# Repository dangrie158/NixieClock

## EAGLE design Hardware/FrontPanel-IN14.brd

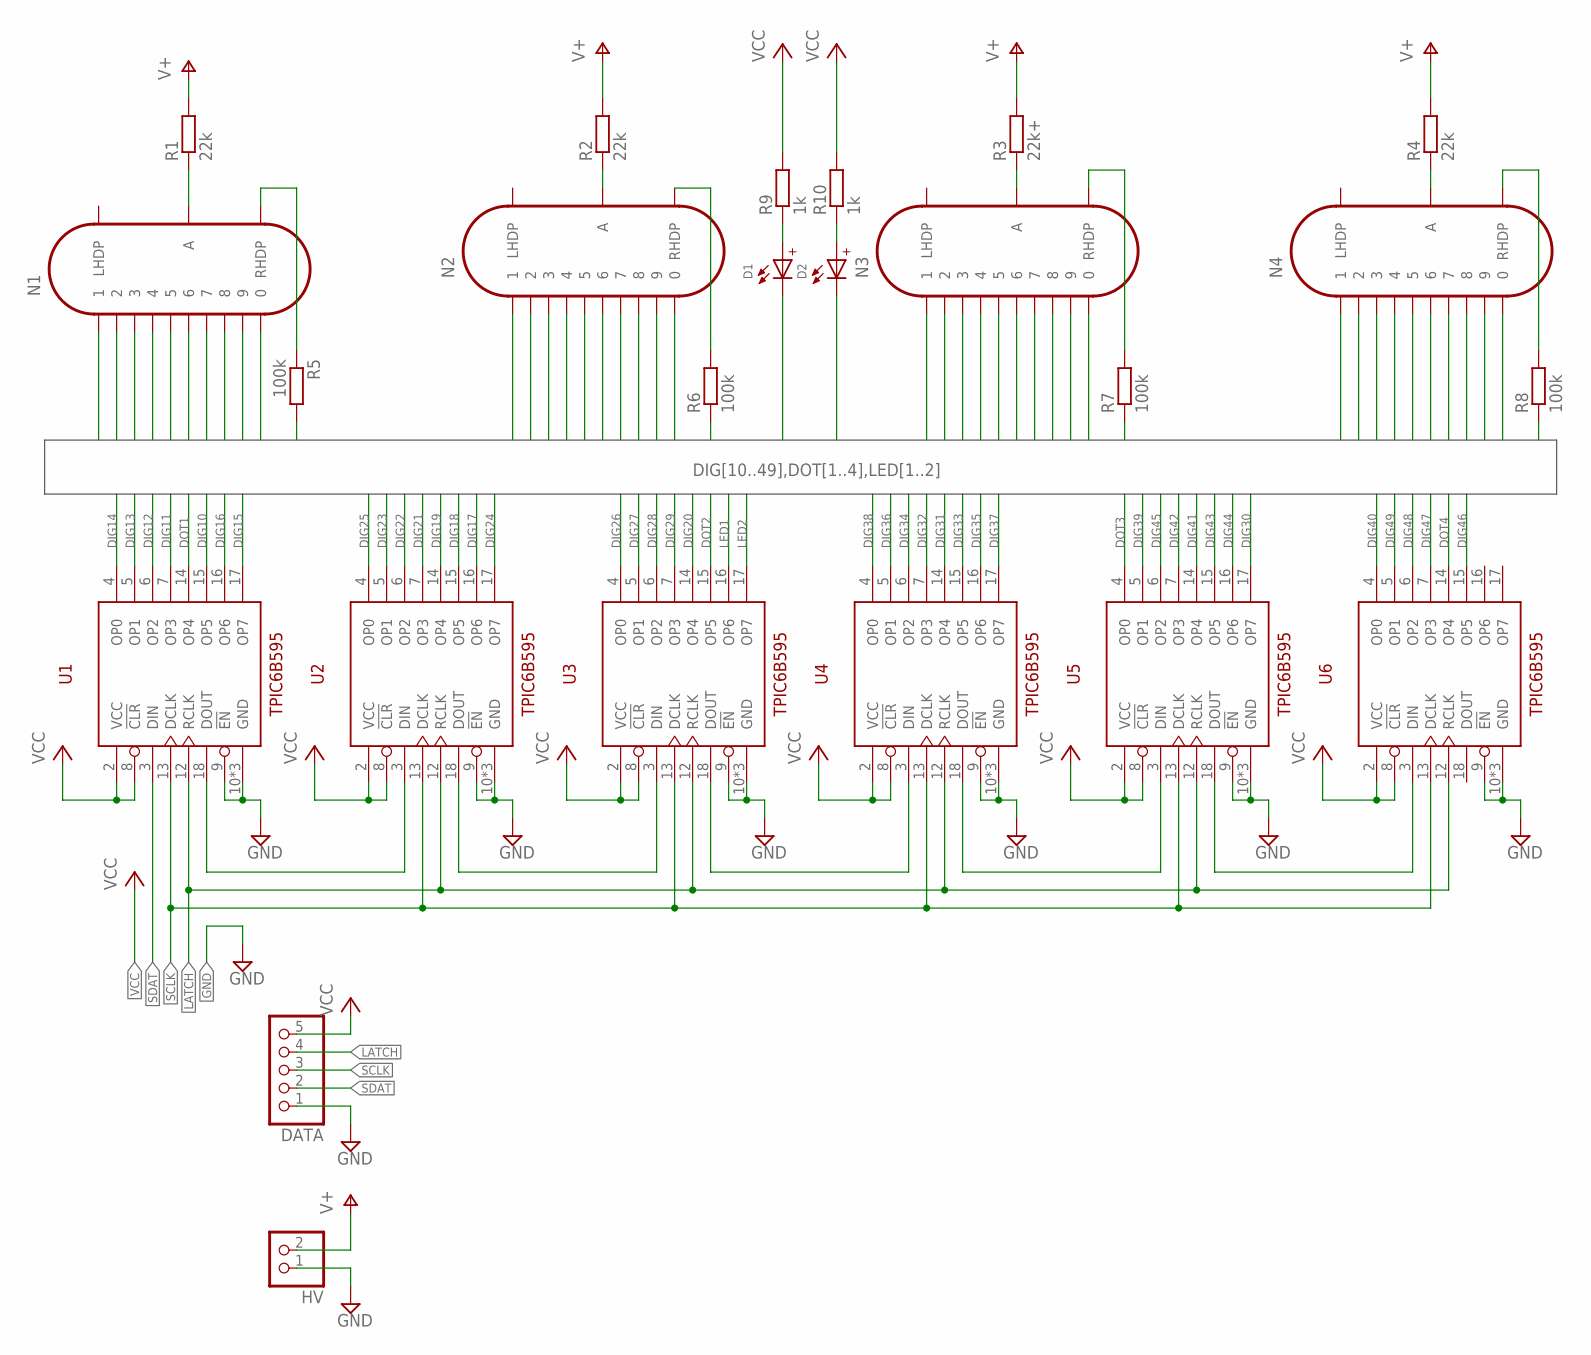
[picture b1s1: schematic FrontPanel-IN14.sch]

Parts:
D1, D2: RED/AMBER; WL-SITW_154141XXBA210
DATA: .1" Header; 1X05
HV: .1" Header; 1X02
N1, N2, N3, N4: IN-14
R1, R2, R4: 22k; 0207/10
R3: 22k+; 0207/10
R5, R6, R7, R8: 100k; 0207/10
R9, R10: 1k; 0207/10
U1, U2, U3, U4, U5, U6: TPIC6B595N; PDIP-20

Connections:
DIG10: N1.0, U1.15 (OP5)
DIG11: N1.1, U1.7 (OP3)
DIG12: N1.2, U1.6 (OP2)
DIG13: N1.3, U1.5 (OP1)
DIG14: N1.4, U1.4 (OP0)
DIG15: N1.5, U1.17 (OP7)
DIG16: N1.6, U1.16 (OP6)
DIG17: N1.7, U2.16 (OP6)
DIG18: N1.8, U2.15 (OP5)
DIG19: N1.9, U2.14 (OP4)
DIG20: N2.0, U3.14 (OP4)
DIG21: N2.1, U2.7 (OP3)
DIG22: N2.2, U2.6 (OP2)
DIG23: N2.3, U2.5 (OP1)
DIG24: N2.4, U2.17 (OP7)
DIG25: N2.5, U2.4 (OP0)
DIG26: N2.6, U3.4 (OP0)
DIG27: N2.7, U3.5 (OP1)
DIG28: N2.8, U3.6 (OP2)
DIG29: N2.9, U3.7 (OP3)
DIG30: N3.0, U5.17 (OP7)
DIG31: N3.1, U4.14 (OP4)
DIG32: N3.2, U4.7 (OP3)
DIG33: N3.3, U4.15 (OP5)
DIG34: N3.4, U4.6 (OP2)
DIG35: N3.5, U4.16 (OP6)
DIG36: N3.6, U4.5 (OP1)
DIG37: N3.7, U4.17 (OP7)
DIG38: N3.8, U4.4 (OP0)
DIG39: N3.9, U5.5 (OP1)
DIG40: N4.0, U6.4 (OP0)
DIG41: N4.1, U5.14 (OP4)
DIG42: N4.2, U5.7 (OP3)
DIG43: N4.3, U5.15 (OP5)
DIG44: N4.4, U5.16 (OP6)
DIG45: N4.5, U5.6 (OP2)
DIG46: N4.6, U6.15 (OP5)
DIG47: N4.7, U6.7 (OP3)
DIG48: N4.8, U6.6 (OP2)
DIG49: N4.9, U6.5 (OP1)
DOT1: R5.2, U1.14 (OP4)
DOT2: R6.1, U3.15 (OP5)
DOT3: R7.1, U5.4 (OP0)
DOT4: R8.1, U6.14 (OP4)
GND: DATA.1, HV.1, U1.9 (!EN), U1.10 (GND), U1.11 (GND), U1.19 (GND), U2.9 (!EN), U2.10 (GND), U2.11 (GND), U2.19 (GND), U3.9 (!EN), U3.10 (GND), U3.11 (GND), U3.19 (GND), U4.9 (!EN), U4.10 (GND), U4.11 (GND), U4.19 (GND), U5.9 (!EN), U5.10 (GND), U5.11 (GND), U5.19 (GND), U6.9 (!EN), U6.10 (GND), U6.11 (GND), U6.19 (GND)
LATCH: DATA.4, U1.12 (RCLK), U2.12 (RCLK), U3.12 (RCLK), U4.12 (RCLK), U5.12 (RCLK), U6.12 (RCLK)
LED1: D1.2 (-), U3.16 (OP6)
LED2: D2.2 (-), U3.17 (OP7)
unnamed: N1.RHDP, R5.1
unnamed: N2.RHDP, R6.2
unnamed: N3.RHDP, R7.2
unnamed: N4.RHDP, R8.2
unnamed: N1.A, R1.1
unnamed: N2.A, R2.1
unnamed: N3.A, R3.1
unnamed: N4.A, R4.1
unnamed: U1.18 (DOUT), U2.3 (DIN)
unnamed: U2.18 (DOUT), U3.3 (DIN)
unnamed: U3.18 (DOUT), U4.3 (DIN)
unnamed: U4.18 (DOUT), U5.3 (DIN)
unnamed: U5.18 (DOUT), U6.3 (DIN)
unnamed: D1.1 (+), R9.1
unnamed: D2.1 (+), R10.1
SCLK: DATA.3, U1.13 (DCLK), U2.13 (DCLK), U3.13 (DCLK), U4.13 (DCLK), U5.13 (DCLK), U6.13 (DCLK)
SDAT: DATA.2, U1.3 (DIN)
V+: HV.2, R1.2, R2.2, R3.2, R4.2
VCC: DATA.5, R9.2, R10.2, U1.2 (VCC), U1.8 (!CLR), U2.2 (VCC), U2.8 (!CLR), U3.2 (VCC), U3.8 (!CLR), U4.2 (VCC), U4.8 (!CLR), U5.2 (VCC), U5.8 (!CLR), U6.2 (VCC), U6.8 (!CLR)

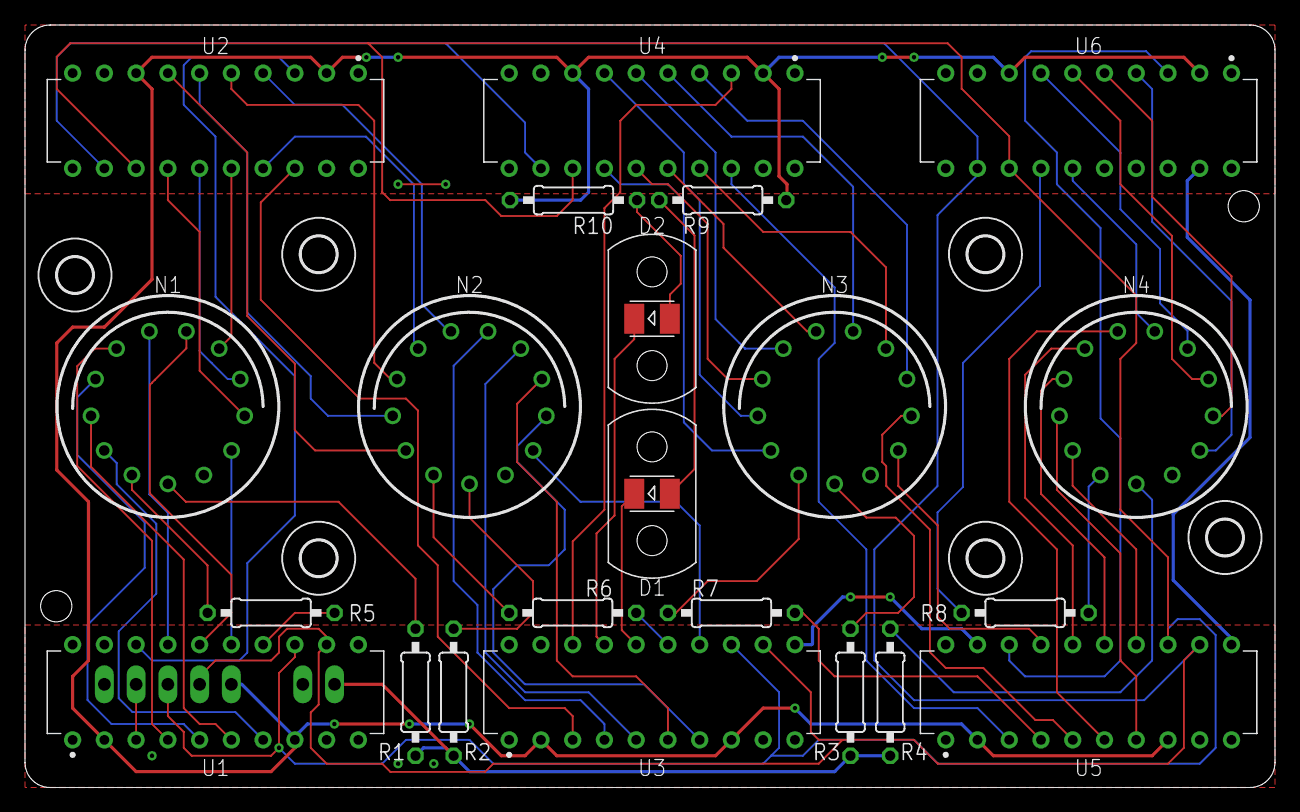
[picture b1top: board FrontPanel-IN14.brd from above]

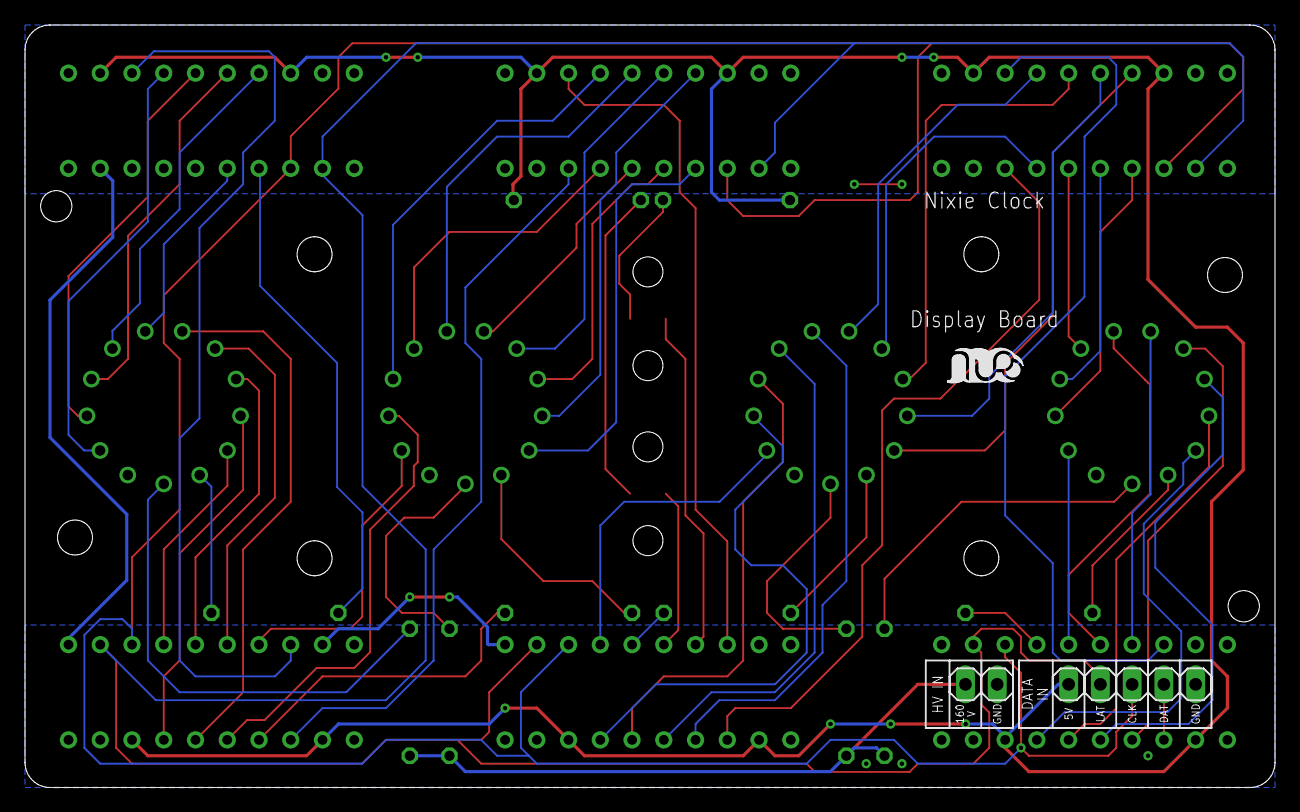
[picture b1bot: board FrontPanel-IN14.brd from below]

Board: 2 copper layers, 100.0 x 61.0 mm, 33 parts (3 on the bottom side), 67 nets.

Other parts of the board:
U$1, U$2, U$3, U$7, U$8, U$9: 2,8
U$4: LOGO-SILKSCREEEN-S
U$5, U$6: MENTOR-1216.1005

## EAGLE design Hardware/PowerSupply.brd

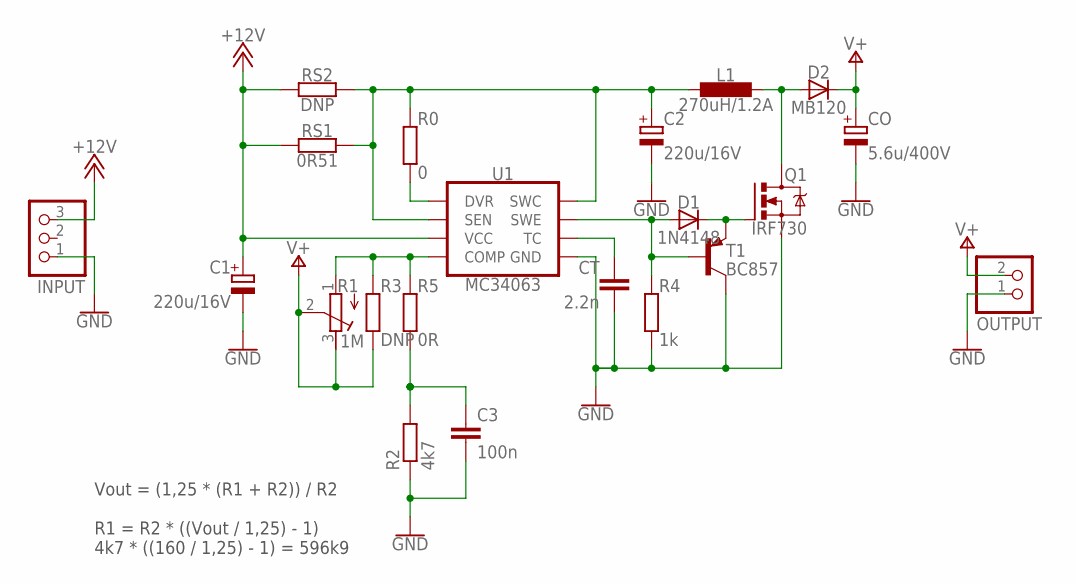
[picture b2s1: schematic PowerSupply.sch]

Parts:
C1, C2: 220u/16V; 140CLH-0810
C3: 100n; C0603K
CO: 5.6u/400V; 153CLV-1010
CT: 2.2n; C0603K
D1: 1N4148; SOD323-W
D2: MB120; DO214AA
INPUT: PINHD-1X3; 1X03
L1: 270uH/1.2A; TC-PIS4728
OUTPUT: PINHD-1X2; 1X02
Q1: IRF730; TO220BV
R0: 0; R0603
R1: 1M; RTRIM64W
R2: 4k7; R0603
R3: DNP; R0603
R4: 1k; R0603
R5: 0R; R0603
RS1: 0R51; R2512
RS2: DNP; R2512
T1: BC857; SOT23-BEC
U1: MC34063; SOIC127P600X175-8

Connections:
+12V: C1.+, INPUT.3, RS1.1, RS2.1, U1.6 (VCC)
GND: C1.-, C2.-, C3.2, CO.-, CT.1, INPUT.1, OUTPUT.1, Q1.S, R2.1, R4.1, T1.C, U1.4 (GND)
unnamed: D1.A, R4.2, T1.B, U1.2 (SWE)
unnamed: D1.C, Q1.G, T1.E
unnamed: R0.2, U1.8 (DVR)
unnamed: D2.A, L1.P$1 (1), Q1.D
unnamed: CT.2, U1.3 (TC)
unnamed: R1.1 (A), R3.2, R5.1, U1.5 (COMP)
unnamed: C3.1, R2.2, R5.2
unnamed: C2.+, L1.P$2 (2), R0.1, RS1.2, RS2.2, U1.1 (SWC), U1.7 (SEN)
V+: CO.+, D2.C, OUTPUT.2, R1.2 (S), R1.3 (E), R3.1

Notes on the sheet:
Vout = (1,25 * (R1 + R2)) / R2 R1 = R2 * ((Vout / 1,25) - 1) 4k7 * ((160 / 1,25) - 1) = 596k9

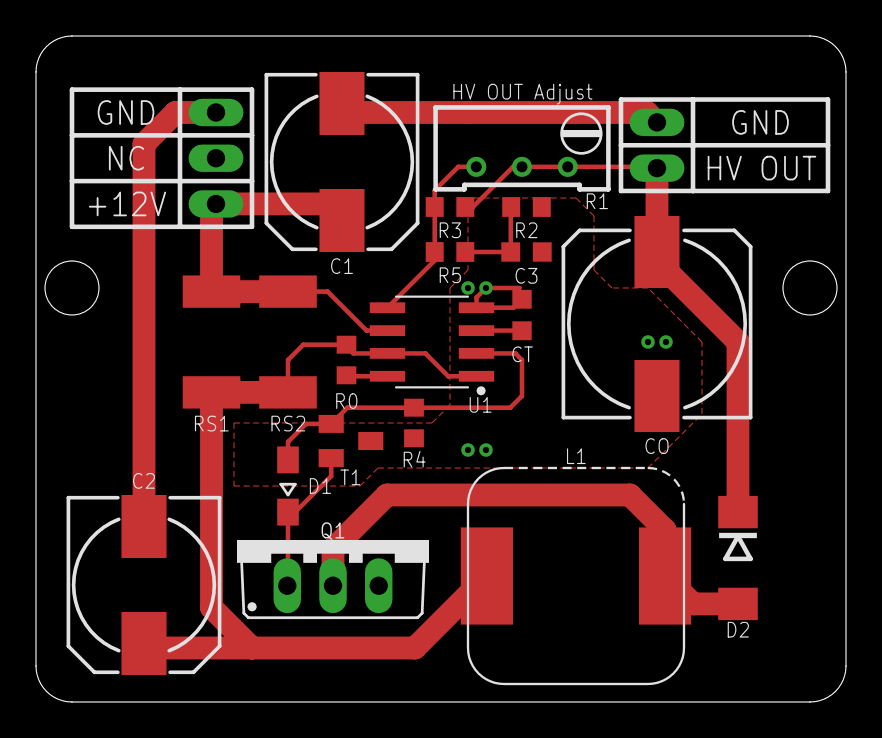
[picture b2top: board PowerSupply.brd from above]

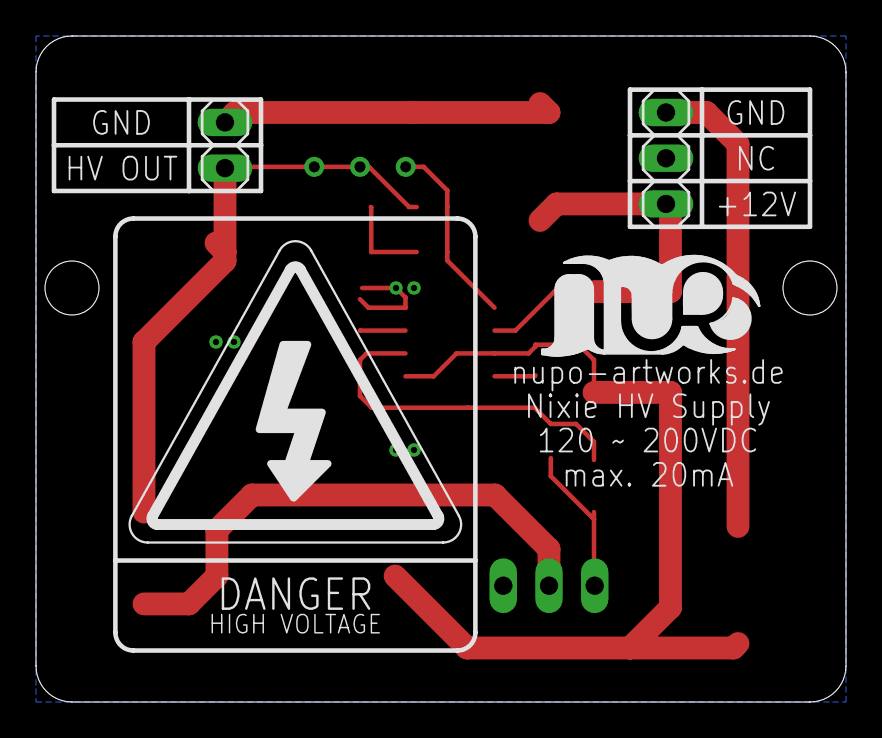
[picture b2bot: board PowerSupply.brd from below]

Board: 2 copper layers, 45.0 x 37.0 mm, 23 parts (4 on the bottom side), 11 nets.

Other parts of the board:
U$1: SIGN-HV
U$2: LOGO-SILKSCREEN

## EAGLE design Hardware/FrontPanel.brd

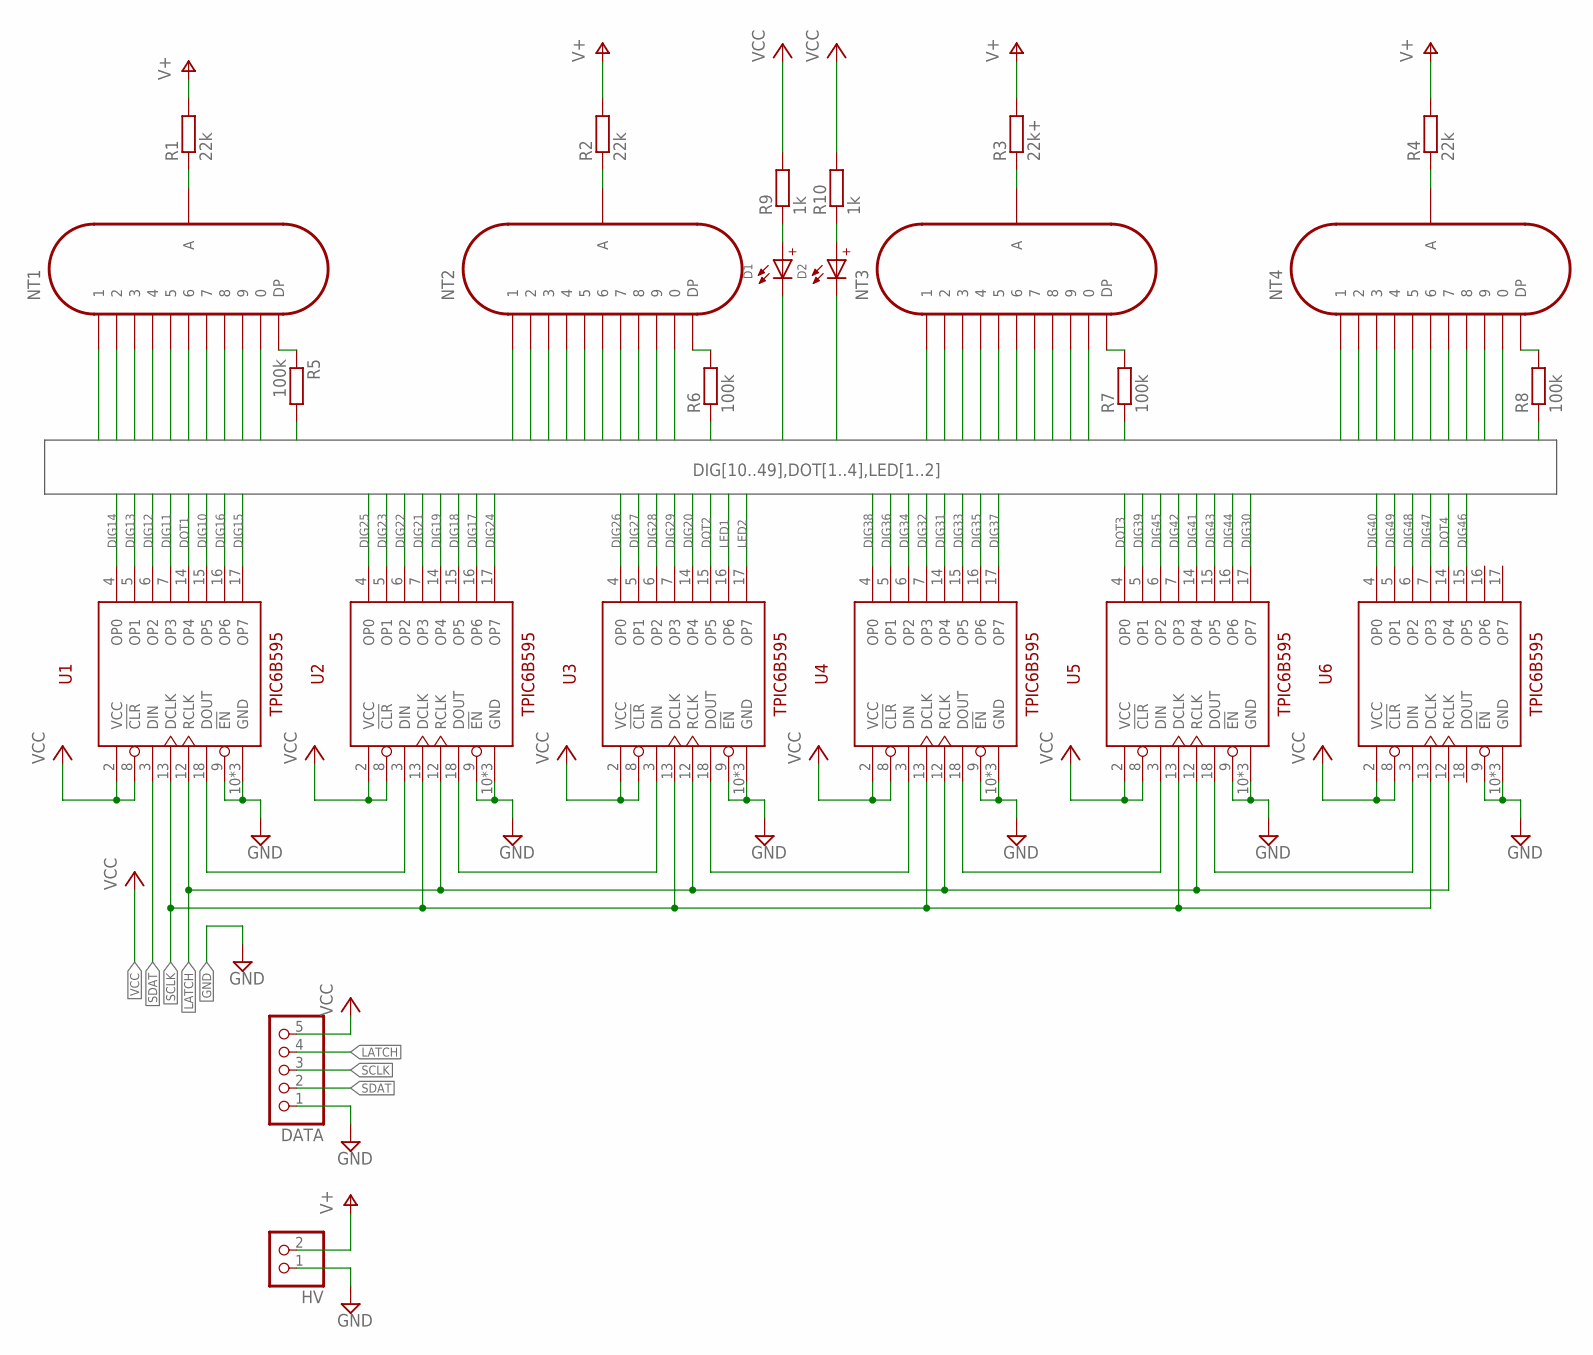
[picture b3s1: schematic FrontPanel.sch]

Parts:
D1, D2: RED/AMBER; WL-SITW_154141XXBA210
DATA: .1" Header; 1X05
HV: .1" Header; 1X02
NT1, NT2, NT3, NT4: IN-12B; IN-12
R1, R2, R4: 22k; 0207/10
R3: 22k+; 0207/10
R5, R6, R7, R8: 100k; 0207/10
R9, R10: 1k; 0207/10
U1, U2, U3, U4, U5, U6: TPIC6B595N; PDIP-20

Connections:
DIG10: NT1.0, U1.15 (OP5)
DIG11: NT1.1, U1.7 (OP3)
DIG12: NT1.2, U1.6 (OP2)
DIG13: NT1.3, U1.5 (OP1)
DIG14: NT1.4, U1.4 (OP0)
DIG15: NT1.5, U1.17 (OP7)
DIG16: NT1.6, U1.16 (OP6)
DIG17: NT1.7, U2.16 (OP6)
DIG18: NT1.8, U2.15 (OP5)
DIG19: NT1.9, U2.14 (OP4)
DIG20: NT2.0, U3.14 (OP4)
DIG21: NT2.1, U2.7 (OP3)
DIG22: NT2.2, U2.6 (OP2)
DIG23: NT2.3, U2.5 (OP1)
DIG24: NT2.4, U2.17 (OP7)
DIG25: NT2.5, U2.4 (OP0)
DIG26: NT2.6, U3.4 (OP0)
DIG27: NT2.7, U3.5 (OP1)
DIG28: NT2.8, U3.6 (OP2)
DIG29: NT2.9, U3.7 (OP3)
DIG30: NT3.0, U5.17 (OP7)
DIG31: NT3.1, U4.14 (OP4)
DIG32: NT3.2, U4.7 (OP3)
DIG33: NT3.3, U4.15 (OP5)
DIG34: NT3.4, U4.6 (OP2)
DIG35: NT3.5, U4.16 (OP6)
DIG36: NT3.6, U4.5 (OP1)
DIG37: NT3.7, U4.17 (OP7)
DIG38: NT3.8, U4.4 (OP0)
DIG39: NT3.9, U5.5 (OP1)
DIG40: NT4.0, U6.4 (OP0)
DIG41: NT4.1, U5.14 (OP4)
DIG42: NT4.2, U5.7 (OP3)
DIG43: NT4.3, U5.15 (OP5)
DIG44: NT4.4, U5.16 (OP6)
DIG45: NT4.5, U5.6 (OP2)
DIG46: NT4.6, U6.15 (OP5)
DIG47: NT4.7, U6.7 (OP3)
DIG48: NT4.8, U6.6 (OP2)
DIG49: NT4.9, U6.5 (OP1)
DOT1: R5.2, U1.14 (OP4)
DOT2: R6.1, U3.15 (OP5)
DOT3: R7.1, U5.4 (OP0)
DOT4: R8.1, U6.14 (OP4)
GND: DATA.1, HV.1, U1.9 (!EN), U1.10 (GND), U1.11 (GND), U1.19 (GND), U2.9 (!EN), U2.10 (GND), U2.11 (GND), U2.19 (GND), U3.9 (!EN), U3.10 (GND), U3.11 (GND), U3.19 (GND), U4.9 (!EN), U4.10 (GND), U4.11 (GND), U4.19 (GND), U5.9 (!EN), U5.10 (GND), U5.11 (GND), U5.19 (GND), U6.9 (!EN), U6.10 (GND), U6.11 (GND), U6.19 (GND)
LATCH: DATA.4, U1.12 (RCLK), U2.12 (RCLK), U3.12 (RCLK), U4.12 (RCLK), U5.12 (RCLK), U6.12 (RCLK)
LED1: D1.2 (-), U3.16 (OP6)
LED2: D2.2 (-), U3.17 (OP7)
unnamed: NT1.LHDP (DP), R5.1
unnamed: NT2.LHDP (DP), R6.2
unnamed: NT3.LHDP (DP), R7.2
unnamed: NT4.LHDP (DP), R8.2
unnamed: NT1.A, R1.1
unnamed: NT2.A, R2.1
unnamed: NT3.A, R3.1
unnamed: NT4.A, R4.1
unnamed: U1.18 (DOUT), U2.3 (DIN)
unnamed: U2.18 (DOUT), U3.3 (DIN)
unnamed: U3.18 (DOUT), U4.3 (DIN)
unnamed: U4.18 (DOUT), U5.3 (DIN)
unnamed: U5.18 (DOUT), U6.3 (DIN)
unnamed: D1.1 (+), R9.1
unnamed: D2.1 (+), R10.1
SCLK: DATA.3, U1.13 (DCLK), U2.13 (DCLK), U3.13 (DCLK), U4.13 (DCLK), U5.13 (DCLK), U6.13 (DCLK)
SDAT: DATA.2, U1.3 (DIN)
V+: HV.2, R1.2, R2.2, R3.2, R4.2
VCC: DATA.5, R9.2, R10.2, U1.2 (VCC), U1.8 (!CLR), U2.2 (VCC), U2.8 (!CLR), U3.2 (VCC), U3.8 (!CLR), U4.2 (VCC), U4.8 (!CLR), U5.2 (VCC), U5.8 (!CLR), U6.2 (VCC), U6.8 (!CLR)

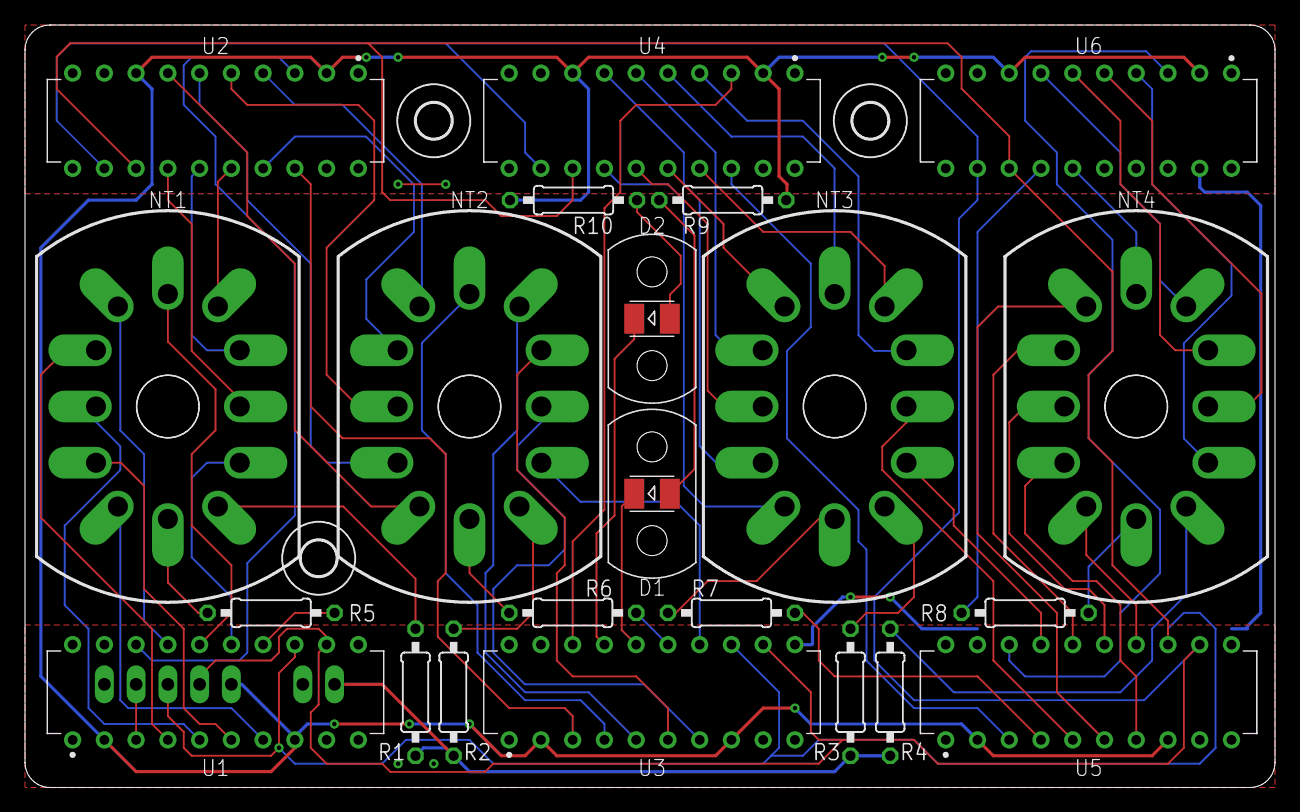
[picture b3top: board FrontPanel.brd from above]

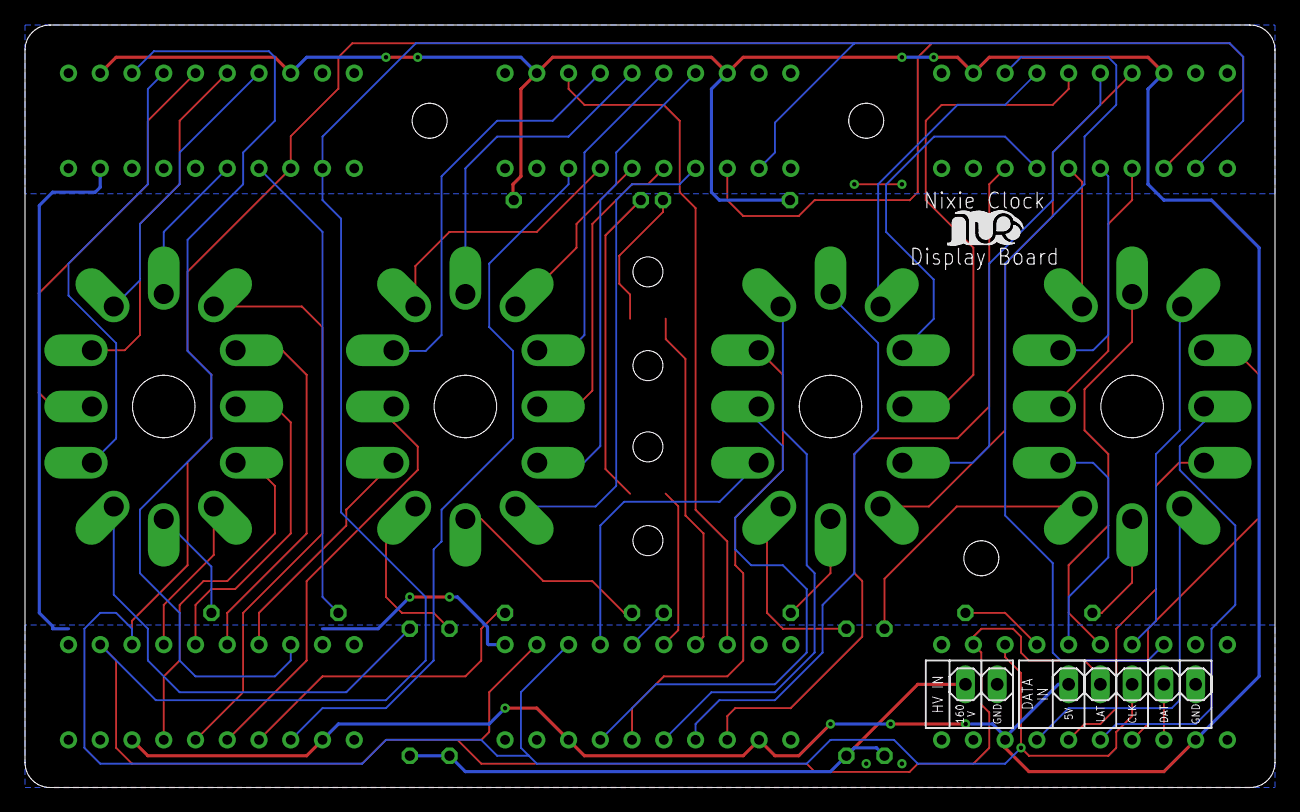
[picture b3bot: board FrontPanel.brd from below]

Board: 2 copper layers, 100.0 x 61.0 mm, 30 parts (3 on the bottom side), 67 nets.

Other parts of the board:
U$1, U$2, U$3: 2,8
U$4: LOGO-SILKSCREEEN-S
U$5, U$6: MENTOR-1216.1005

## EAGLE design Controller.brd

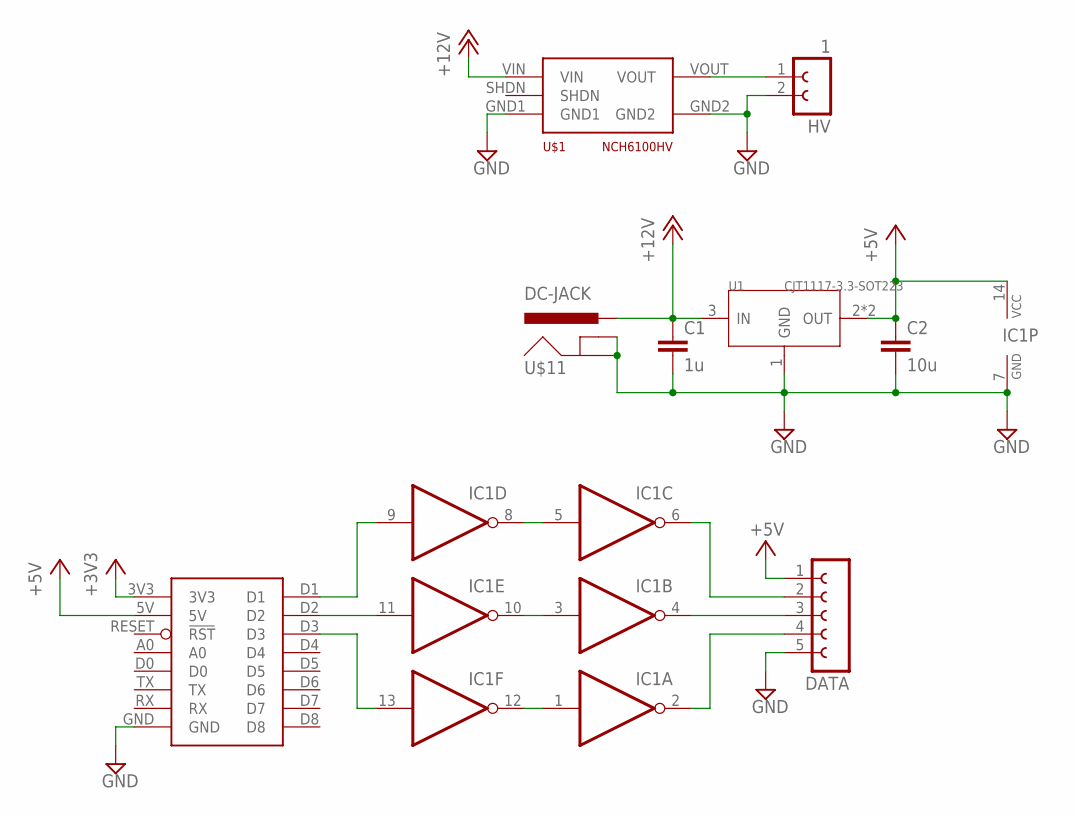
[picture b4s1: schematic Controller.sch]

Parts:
C1: 1u; C0603K
C2: 10u; C0603K
DATA: FE05W
HV: 1; FE02W
IC1: 74HCT04D; SO-14
U1: CJT1117-3.3-SOT223; SOT-223
U$1: NCH6100HV
U$11: DC-JACK; POWER_JACK_PTH
U$12: WEMOS-D1; WEMOS-D1-MINI

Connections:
+3V3: U$12.3V3
+5V: C2.1, DATA.1, IC1.14 (VCC), U1.2 (OUT), U1.TER (OUT), U$12.5V
+12V: C1.1, U1.3 (IN), U$1.VIN, U$11.PWR
GND: C1.2, C2.2, DATA.5, HV.2, IC1.7 (GND), U1.1 (GND), U$1.GND1, U$1.GND2, U$11.GND, U$11.GNDBREAK, U$12.GND
unnamed: HV.1, U$1.VOUT
unnamed: IC1.5 (I), IC1.8 (O)
unnamed: IC1.3 (I), IC1.10 (O)
unnamed: IC1.1 (I), IC1.12 (O)
unnamed: DATA.3, IC1.4 (O)
unnamed: IC1.13 (I), U$12.D3
unnamed: DATA.4, IC1.2 (O)
unnamed: DATA.2, IC1.6 (O)
unnamed: IC1.9 (I), U$12.D1
unnamed: IC1.11 (I), U$12.D2

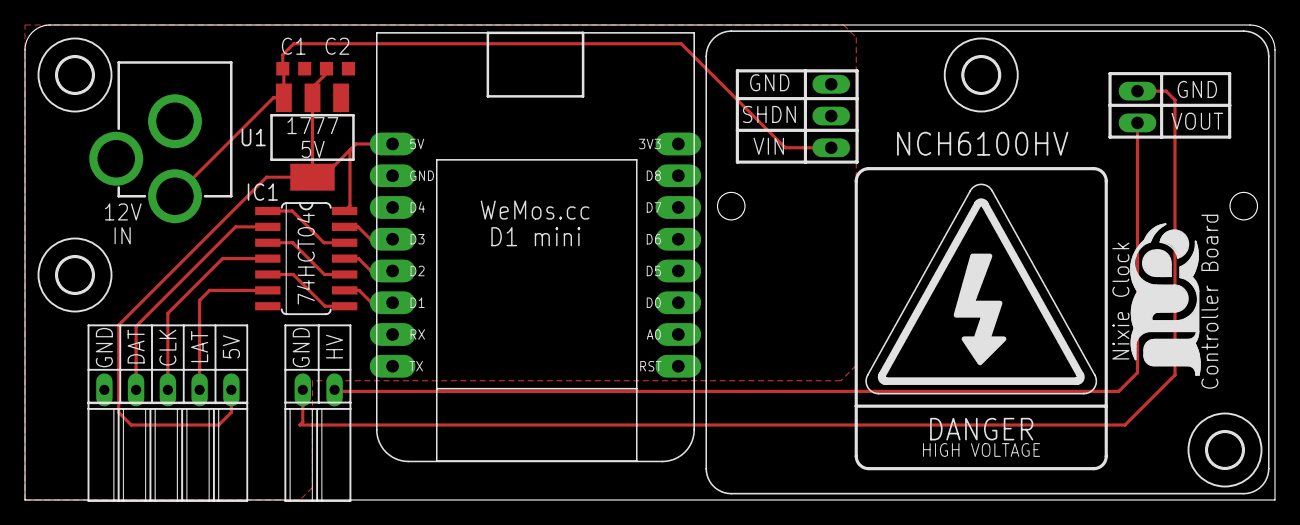
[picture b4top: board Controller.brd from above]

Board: 2 copper layers, 100.0 x 38.0 mm, 14 parts (0 on the bottom side), 13 nets.

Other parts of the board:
U$2: LOGO-SILKSCREEN
U$3, U$4, U$5, U$6: 2,8

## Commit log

2018-12-17 added script to automatically create panel
2018-12-18 added second inverter stage to controller to have non-inverted logic on the outputs
2018-12-18 switched to smd LEDs and added Light-Pipes
2018-12-18 repositioned labels on connector
2018-12-18 reduced loop area for high-voltage line
2018-12-18 added additional mounting hole
2018-12-18 moved mounting hole to more accessible location
2018-12-18 fixed airwire in front panel and updated panel
2018-12-18 updated DC Boost Converter silkscreen
2018-12-19 moved hardware files to subfolder
2018-12-19 added ordered gerber files
2018-12-19 initial firmware commit
2018-12-19 removed config header from index to keep API key safe
2018-12-20 implemented basic functionality for firmware
2018-12-21 added save-state initialitatino at start of setup
2018-12-25 fixed ERC errors
2018-12-29 added DC Boost Converter Module Designfiles and Simulation
2018-12-29 Added display gtest on startup
2018-12-29 renamed power supply design files
2018-12-29 added power supply board gerbers
2018-12-29 fixed display pin mapping and test function
2018-12-29 added passphrase display while in AP-setup mode
2018-12-29 fixed timezone offset problem
2019-01-04 fixed digit pin mapping
2019-01-04 added repeated password to match minimum length requirement
2019-01-06 split display function into separate parts to enable PWM dimming of the display
2019-01-06 implemented time-dependent dimming
2019-01-06 fixed time-dependent dimming
2019-01-06 autoformatted source
2019-01-07 undefined DEBUG output to stop flashing display in dimmed mode
2020-01-01 added IN14 front panel variant
2020-01-11 added lasercut cases
2020-02-01 added different pin definitions for IN-12 and IN-14 variants
2020-02-01 updated IN-14 Case to fix space issues
2022-03-30 added dependencies and updated dependencies to newest version
2022-03-30 increased upload speed
2023-02-21 added config containing TZDB API key to .gitignore

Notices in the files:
parts and their libraries:
Wurth_Elektronik_Optoelectronics_rev17b: Copyright: Würth Elektronik
